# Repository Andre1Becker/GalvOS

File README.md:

# GalvOS

---

## What Is GalvOS?

GalvOS replaces the original control board of an RGB galvo laser projector (specifically the Mikoy 5W) with an ESP32-S3-based system. The result is a firmware platform that is more capable, fully open, and frankly more fun to work with than whatever the OEM shipped.

The origin story: the stock firmware couldn't dim the laser — it was full-brightness or nothing. What started as a quick bug investigation turned into a complete hardware and firmware replacement. Classic "Well, that escalated quickly..." moment.

**Key capabilities:**

- 16-bit galvo DAC (vs. OEM 12-bit) via SPI DAC8562
- Browser-based WebUI — no app install, works from any phone or desktop
- DMX-512, Art-Net, sACN/E1.31, and OSC input; Ether Dream and Helios (network) DAC protocols
- ILDA file playback from SD card
- Per-point laser modulation with full RGB PWM control
- BPM-synced show engine: global tempo clock (Tap/DMX/Manual), preset sequencer, and an 8-slot modulation matrix (LFO/Noise/Envelope/Step-Sequencer → any live pattern parameter)
- Watchdog, scan-command activity and E-stop interfaces — [safety qualification remains open](hardware/reviews/2026-09-14-shutdown-boundary.md)
- Point optimizer pipeline with adaptive density, S-curve blanking, and ringing compensation
- Camera-in-the-loop auto-tuning of optimizer parameters via a companion Python tool (see [Chapter 6](docs/06-camera-autotuning.md))
- Community Presets — browse, download, and activate GitHub-hosted preset bundles straight from the WebUI
- Temperature monitoring (up to 5× DS18B20 sensors)

---

## Full Feature List

Yes, all of this is real, and yes, it's all running on a 6 Freedom Money ($) microcontroller.
(That exclude all the other components you need - but hey, sounds much more impressive this way:-) )

### Output & Rendering

| Feature | What it does |
| --- | --- |
| 16-bit galvo DAC (DAC8562) | 4× the resolution of the OEM's 12-bit — lines that were jagged are now just... lines. |
| 9-stage point optimizer pipeline | Turns "draw a hexagon" into a stream the mirrors can physically survive — corner dwell, blanking, velocity/acceleration clamp, ZV ringing compensation. |
| 8 optimizer profiles (Vector, Smooth, Waves, Wireframe, MultiObject, Particles, Trails, Text) | One-size-fits-all optimizer settings don't exist, so pick per preset class instead. Auto-switches with the active preset. |
| Curvature-adaptive resampling | Spends points where the path actually bends and thins them out on straight runs, instead of pretending every millimetre is equally interesting. |
| Jump-order optimization (nearest-neighbour + 2-opt) | Reorders which segment gets drawn when, so the beam stops zigzagging across the canvas with the laser off. |
| Optimizer live telemetry | Lit/blank counts, truncated points, jump distance, which budget stage fired — tuning with numbers instead of vibes. |
| Smart Defaults button | Computes sane optimizer parameters from your kpps and frame budget. For when guessing sliders gets old. |
| Adjustable galvo sample rate (12–60 kpps) with Autotune | Binary-searches the highest rate your hardware handles before it starts buffering complaints. |
| CIE 1931 gamma correction | γ≈2.2 so "50% brightness" actually looks like 50% brightness to your eyeballs, not to a linear sensor. |
| Projection zone clipping | Draw a polygon, laser respects it. Points outside get blanked instead of redecorating your neighbor's wall. |
| Grid warp (keystone / surface correction) | Up to 5×5 control points to bend the image onto an off-axis or non-flat wall — corrects everything the projector draws, presets to ILDA files. |
| Brightness compensation grid | Same grid editor aimed at photons: evens out the exposure falloff you get from throw distance and angle. |
| Model-based inverse filter | Per-axis deconvolution of the galvo's measured resonance, applied to every point — the mirrors track the commanded path instead of ringing around it. |
| Output pre-scale | Shrinks the image proportionally so extreme corners stay in the galvo's linear range, instead of being flattened by the DAC clamp. |

### Patterns & Effects

| Feature | What it does |
| --- | --- |
| Built-in preset library (Geometry, Waves, 3D, Scenes, math curves) | A whole gallery of shapes so you don't have to parametrize a Lissajous curve at 2 AM. |
| Auto-rotation (independent X/Y/Z) + static rotation offset | Spin any pattern on any axis, at its own speed, because static geometry is for cowards. |
| 7 color animation modes (Gradient, Chase, Strobe, Pulse, Twinkle, Flip, Seg) | Layer a light show on top of any preset's own color without touching its code. |
| Points-Only Mode | Turns any pattern into a dot cloud with configurable fade-in/out and fade direction — instant particle show. |
| True Kaleidoscope (dihedral mirror-fold, 2/4/6-fold) + Radial Repeat mode & Mirror | Symmetric multiplication of whatever's on screen, because one hexagon is never enough. |
| Global BPM clock (Manual / Tap Tempo / DMX) | The whole show keeps a beat — priority DMX > Tap > Manual, with a big satisfying TAP button. |
| Preset Sequencer | A BPM-synced set list: walk presets step by step, beat-quantized, with optional blank transitions. Never auto-starts on boot — Class 4 lasers don't get autoplay. |
| Modulation engine (8 slots × 16 bindings) | LFOs, noise, multi-point envelopes, and step sequencers routed onto scale, rotation, hue, speed, density... Patterns that breathe on their own. |
| Modular modules: Camera, Duplicator, Spatial Noise, Dotter | Self-registering firmware modules that add 3D camera moves, frame cloning (grid/radial/spiral), organic wobble, and dot scatter — the UI discovers them automatically. |
| Freehand Paint tab | Draw with your finger or mouse, project it as vectors. Shape tools, mirror modes, undo/redo, and text insertion included for people who can't draw circles. |
| Laser Welding effect | A travelling torch head with a fading afterglow and ballistic sparks, rendered from the same Paint canvas. Pure theatre, and worth it. |
| SVG import | Load a vector drawing in the browser, simplify it to fit the point budget, and project it. Files can live on the SD card too. |
| Per-segment colors | Give a polygon or star a different color per edge, with an optional travelling animation. |
| Laser Text mode | 3 fonts, 10 animations (scroll, bounce, typewriter, Star Wars crawl,...), up to 127 characters. |
| Countdown timer with laser payoff | Set a timer, and when it hits zero: show text or fire off an ILDA file. Genuinely useful for events. |
| Community Presets (GitHub-hosted) | Browse a shared preset library straight from GitHub in the WebUI, download to the device, activate with one tap — each bundle carries a full optimizer tuning plus playback params. Now the internet can pick your colors too. |
| Community Preset Builder | Offline browser tool ([`community-presets/builder.html`](community-presets/builder.html)) for creating those bundles — for people who'd rather drag sliders than write C++. Advanced Mode even has a point/curve editor that exports C++ snippets for new built-in presets. |

### Control Inputs

| Feature | What it does |
| --- | --- |
| DMX-512 input (MAX485, 25 channels) | Talks to any real lighting desk like a grown-up fixture. |
| Art-Net input | DMX over Ethernet/Wi-Fi for the desk-less crowd. |
| sACN / E1.31 input | The standards-blessed way to do DMX over IP multicast. Same channel map, lowest priority of the three DMX-shaped sources. |
| OSC input | `/galvos/*` on UDP 9000 — preset, color, speed, brightness, and override from TouchOSC & friends. |
| Ether Dream protocol receiver | Laser software that speaks Ether Dream can stream point data straight to the projector. |
| Helios DAC network emulation | Helios point-stream framing over TCP 7768. The USB variant is not implemented (TinyUSB vendor class vs. the USB-CDC console). |
| Live software DMX console (WebUI) | 25 sliders, no physical desk required, with instant test patterns (red circle, rainbow). |
| WebUI override priority | WebUI wins over DMX on demand — for when you need to grab manual control mid-show. |
| Master dimmer (WebUI + DMX CH1 combined) | One dial to rule the overall brightness, regardless of source. |

### Storage & Playback

| Feature | What it does |
| --- | --- |
| ILDA file playback from SD card | Plays the industry-standard laser show format straight off a memory card — subfolders, live speed/size/color-override controls, browser upload included. |
| Playlist manager | Queue multiple ILDA files with per-entry loop count and pause duration. |
| PSRAM budget guard for ILDA files | Files too big to load safely are grayed out *before* you play them, instead of rebooting the controller mid-show. |
| SD auto-mount watcher | Insert a card whenever — it gets picked up within 5 seconds. Eject means eject, until you say otherwise. |
| SD file management from the browser | Download, rename, or delete `.ild` and `.svg` files on the card without pulling it out of the projector. |
| Independent SPI3 bus for SD | SD reads no longer corrupt the DAC output mid-frame — SD card lives on its own SPI3 bus (GPIO5/6/1/42), fully independent of the DAC's SPI2. |

### Calibration & Tuning

| Feature | What it does |
| --- | --- |
| Galvo geometry calibration | Offset, gain (linked X/Y), swap, invert — dial in a perfectly centered, correctly proportioned image. |
| Color/gamma calibration patterns | White fill, per-channel fill, three-circle white balance, crosshair, grid, DAC range box, official ILDA test pattern. |
| Visibility threshold calibration | Finds each laser diode's "dead zone" so 0–100% brightness maps to what's actually visible instead of a chunk of invisible PWM range. |
| Auto White Balance | Calculates per-channel gain from configured laser power so R/G/B actually look equally bright. |
| Camera-in-the-loop auto-tuning | A USB camera + Optuna search auto-tunes optimizer profiles against measured beam quality — no more "nudge a slider, squint at the wall" loop. See [Chapter 6](docs/06-camera-autotuning.md). |
| Resonance sweep | Drives one axis with a pure sine at a chosen frequency so you can actually measure the galvo's resonance instead of guessing at it. |

### Safety & Reliability

| Feature | What it does |
| --- | --- |
| Hardware E-Stop input | A physical kill switch the firmware cannot override. |
| NE555 scan-fail detection | If the galvo stops moving (or firmware hangs), the laser cuts — hardware-level, no software in the loop. |
| NE555 hardware watchdog | Independent of the ESP32's own watchdog; catches the case where the ESP32 itself locks up. |
| Fail-safe opto-isolated RGB TTL | 10kΩ pull-ups keep every laser channel OFF by default on boot, reset, panic, or brownout. |
| OTA update lockout while armed | Can't push new firmware to a live, armed laser. On purpose. |
| Browser OTA for firmware *and* WebUI | An `/update` page that flashes either partition, reports real error strings, and refuses to auto-reboot into a half-finished update. |
| Safety Assessment card | Live laser-class and audience-distance estimate from your configured power and beam angles. |
| Thermal protection | Up to 5× DS18B20 sensors with per-sensor names and calibration offsets, configurable warn/reduce/shutdown thresholds, auto or manual fan control, and a °C/°F/K display switch. |

### Connectivity & UI

| Feature | What it does |
| --- | --- |
| Browser-based WebUI, installable as a PWA | No app store, no native install — works full-screen from any phone, tablet, or desktop. |
| Three switchable themes | Cyberpunk/Glitch, Terminal CLI, Minimalist Dark — same controls, three personalities, zero flash-of-wrong-theme on reload. |
| Mobile-first safety controls | ARM/DISARM and Master Dimmer pinned in an always-visible top bar, 44 px touch targets — the kill switch never scrolls away. |
| Per-protocol debug logging | A "snitch switch" per network protocol (DMX, Art-Net, Ether Dream, Helios, OSC, sACN) — raw traffic straight into the Log tab. |
| Live Dashboard | Safety status, telemetry, CPU load, temperature history, DAC output rate, and frame composition — all scrolling in real time. |
| Live log console + memory viewer | Streamed over WebSocket, color-coded by severity, plus a heap/PSRAM breakdown by subsystem for hunting leaks. |
| Wi-Fi AP + STA mode, mDNS | Joins your network and answers at `galvOS.local`; falls back to its own WPA-protected access point when the network is unreachable, while still retrying in the background. |
| Static IP / DHCP configuration | For the tinfoil hatters who don't trust DHCP leases. |
| REST API with token auth | Full external control surface — see [API Reference](docs/08-api-reference.md). |
| Factory reset | Nukes all NVS config back to defaults when you've fat-fingered one setting too many. |

---

## Quick Start

Feeling yolo? Take this route then:

1. **Read the [Safety section](docs/01-introduction.md#safety--read-this-first)** — seriously.
2. **Check [Prerequisites](docs/02-prerequisites.md)** — tools and hardware needed.
3. **[Build & Flash](docs/03-build-and-config.md)** — PlatformIO build, firmware + WebUI upload.
4. **[Connect to WebUI](docs/04-ui-guide.md)** — Wi-Fi, browser, done.

No board on the bench yet? Try the WebUI first at **[www.galvos.de](https://www.galvos.de)** — see [Live Simulator](#live-simulator-no-hardware-required) below.

---

## Live Simulator (No Hardware Required)

**[www.galvos.de](https://www.galvos.de)** runs the exact WebUI as a self-contained browser simulation — a fake firmware backend behind the same frontend, no ESP32, no flashing, no install. Click around every tab, fire presets, tune the optimizer, and watch a simulated galvo trace respond, all before you own a single component. Handy for evaluating the UI, planning a build, or just seeing what the fuss is about.

It is **not** identical to a real device — no camera-in-the-loop tuning, no actual laser/galvo output, and it can lag a patch or two behind the firmware/UI shipped here (maintained by hand, see [Known Issues](docs/10-known-issues-and-todos.md#ui-issues)). For the real thing, [build one](docs/03-build-and-config.md).

---

## Documentation

Need a good sleep aid? This is the one for you here:

| Chapter | Description |
| --- | --- |
| [01 — Introduction](docs/01-introduction.md) | Project background, safety, disclaimer, hardware overview |
| [02 — Prerequisites](docs/02-prerequisites.md) | Tools, hardware, software, and skills needed |
| [03 — Build & Configuration](docs/03-build-and-config.md) | PlatformIO setup, all configurable parameters, flash instructions |
| [04 — UI Guide](docs/04-ui-guide.md) | Complete walkthrough of all WebUI tabs and controls |
| [05 — The Optimizer](docs/05-optimizer.md) | Deep-dive into the point optimizer pipeline |
| [06 — Auto-Tuning (CAM-based)](docs/06-camera-autotuning.md) | Automated optimizer tuning via `scripts/optimizeGalvo/optimizeGalvo.py` and a USB camera |
| [07 — Troubleshooting](docs/07-troubleshooting.md) | Common problems and how to solve them |
| [08 — API Reference](docs/08-api-reference.md) | REST API endpoints for integration and automation |
| [09 — Contributing](docs/09-contributing.md) | How to contribute, code style, patch workflow |
| [10 — Known Issues & To-dos](docs/10-known-issues-and-todos.md) | Open bugs, missing features, planned work |
| [11 — Glossary & Terminology](docs/11-glossary.md) | All (no but most) abbreviations and technical terms explained |

Release history: [CHANGELOG.md](CHANGELOG.md).

---

## Hardware at a Glance

Don't like one's and zero's that much? Well, this one is for you then:

| Component | Part |
| --- | --- |
| MCU | ESP32-S3-WROOM-1 N16R8 (16 MB Flash, 8 MB OPI PSRAM) |
| DAC | DAC8562 (16-bit, dual-channel, SPI) |
| Output Stage | OPA4134UA quad op-amp — differential ±5V galvo drive |
| Galvo Set | Jolooyo JY-15K-BL (15 kpps, ±20° optical) |
| Laser Driver | MN-1M5AT (3-channel constant-current buck, active-HIGH) |
| DMX | MAX485 module (receive-only, XLR) |
| Safety | NE555 scan-fail + NE555 hardware watchdog, 6N137 optocouplers |
| Temperature | DS18B20 × up to 5, 1-Wire bus |
| Power | HW-613 buck converter (+5V rail); external ±15V galvo PSU |
| Construction | Perfboard 15 × 9 cm; Gerber File for custom PCB is in progress |

Full netlist: [`hardware/`](hardware/)

---

## Repository Structure

```text
GalvOS/
├── src/                    # Firmware source (C++, Arduino/PlatformIO)
│   ├── control/            # DMX, Art-Net, safety control
│   ├── ilda/               # ILDA file parser
│   ├── net/                # WebUI server, REST API, Art-Net/sACN/OSC/Ether Dream/Helios receivers
│   ├── output/             # Galvo ISR, DAC output, RGB PWM
│   ├── patterns/           # Pattern engine, presets, optimizer
│   ├── safety/             # E-Stop, watchdog, scan-fail
│   ├── sensors/            # DS18B20, temperature monitoring
│   ├── storage/            # SD card, ILDA playlists, SVG storage
│   └── util/               # Shared utilities (log buffer, CPU/mem monitors, PSRAM scratch)
├── include/
│   ├── config.h            # Runtime config struct, optimizer defaults
│   └── pinmap.h            # All GPIO assignments
├── data/
│   └── index.html          # WebUI (single-file PWA, served via LittleFS)
├── community-presets/      # GitHub-hosted community preset library
│   ├── index.json          # Preset index fetched by the WebUI's GitHub Browser
│   ├── builder.html        # Community Preset Builder (offline browser tool, no backend)
│   └── *.json              # The preset bundles themselves
├── test/                   # Host-side (native) test suites
├── hardware/               # Netlist, schematics, wiring diagrams
├── scripts/
│   ├── upload_all.py       # PlatformIO target: flash firmware + LittleFS
│   ├── gzip_assets.py      # Pre-build hook: gzip data/ assets
│   ├── test_protocols.py   # Manual Ether Dream/Helios stream test client
│   └── optimizeGalvo/      # Camera-in-the-loop auto-tuning tool (see docs/06)
├── docs/                   # Full documentation (you are here)
│   ├── index.html          # Standalone WebUI simulator (served at galvos.de, no backend)
│   └── assets/             # Screenshots, diagrams, photos
├── platformio.ini          # Build configuration
└── partitions.csv          # Flash partition table
```

---

## ⚠️ SAFETY WARNING — READ BEFORE PROCEEDING

(I know - BORING! But hey - at least you read this far. So keep going!)

**This project involves CLASS IIIB or CLASS IV laser devices.**

Lasers at these power levels are capable of causing **immediate and permanent eye injury** and skin burns, and can ignite materials at close range.

- **Never** look into the beam or at specular (mirror-like) reflections.
- **Always** use appropriate laser safety eyewear — OD rating matched to your specific wavelengths and power level.
- **Never** operate the laser without proper enclosure or beam stops in place.
- By modifying this device, the original CE marking and safety certification are **void**.
- **You are solely responsible** for the safe operation of any device built using this project.
- Check your local laws — modifying laser equipment may require licensing in your jurisdiction.

> 🔴 **This project is intended for experienced makers and engineers who understand laser safety. Treat every beam as dangerous until proven otherwise.**

---

## License

- **Firmware & Software:** [GNU General Public License v3.0](LICENSE)
- **Hardware Designs:** [CERN Open Hardware License v2 — Strongly Reciprocal (CERN-OHL-S)](https://ohwr.org/cern_ohl_s_v2.txt)

Contributions welcome under the same license terms. See [Contributing](docs/09-contributing.md).

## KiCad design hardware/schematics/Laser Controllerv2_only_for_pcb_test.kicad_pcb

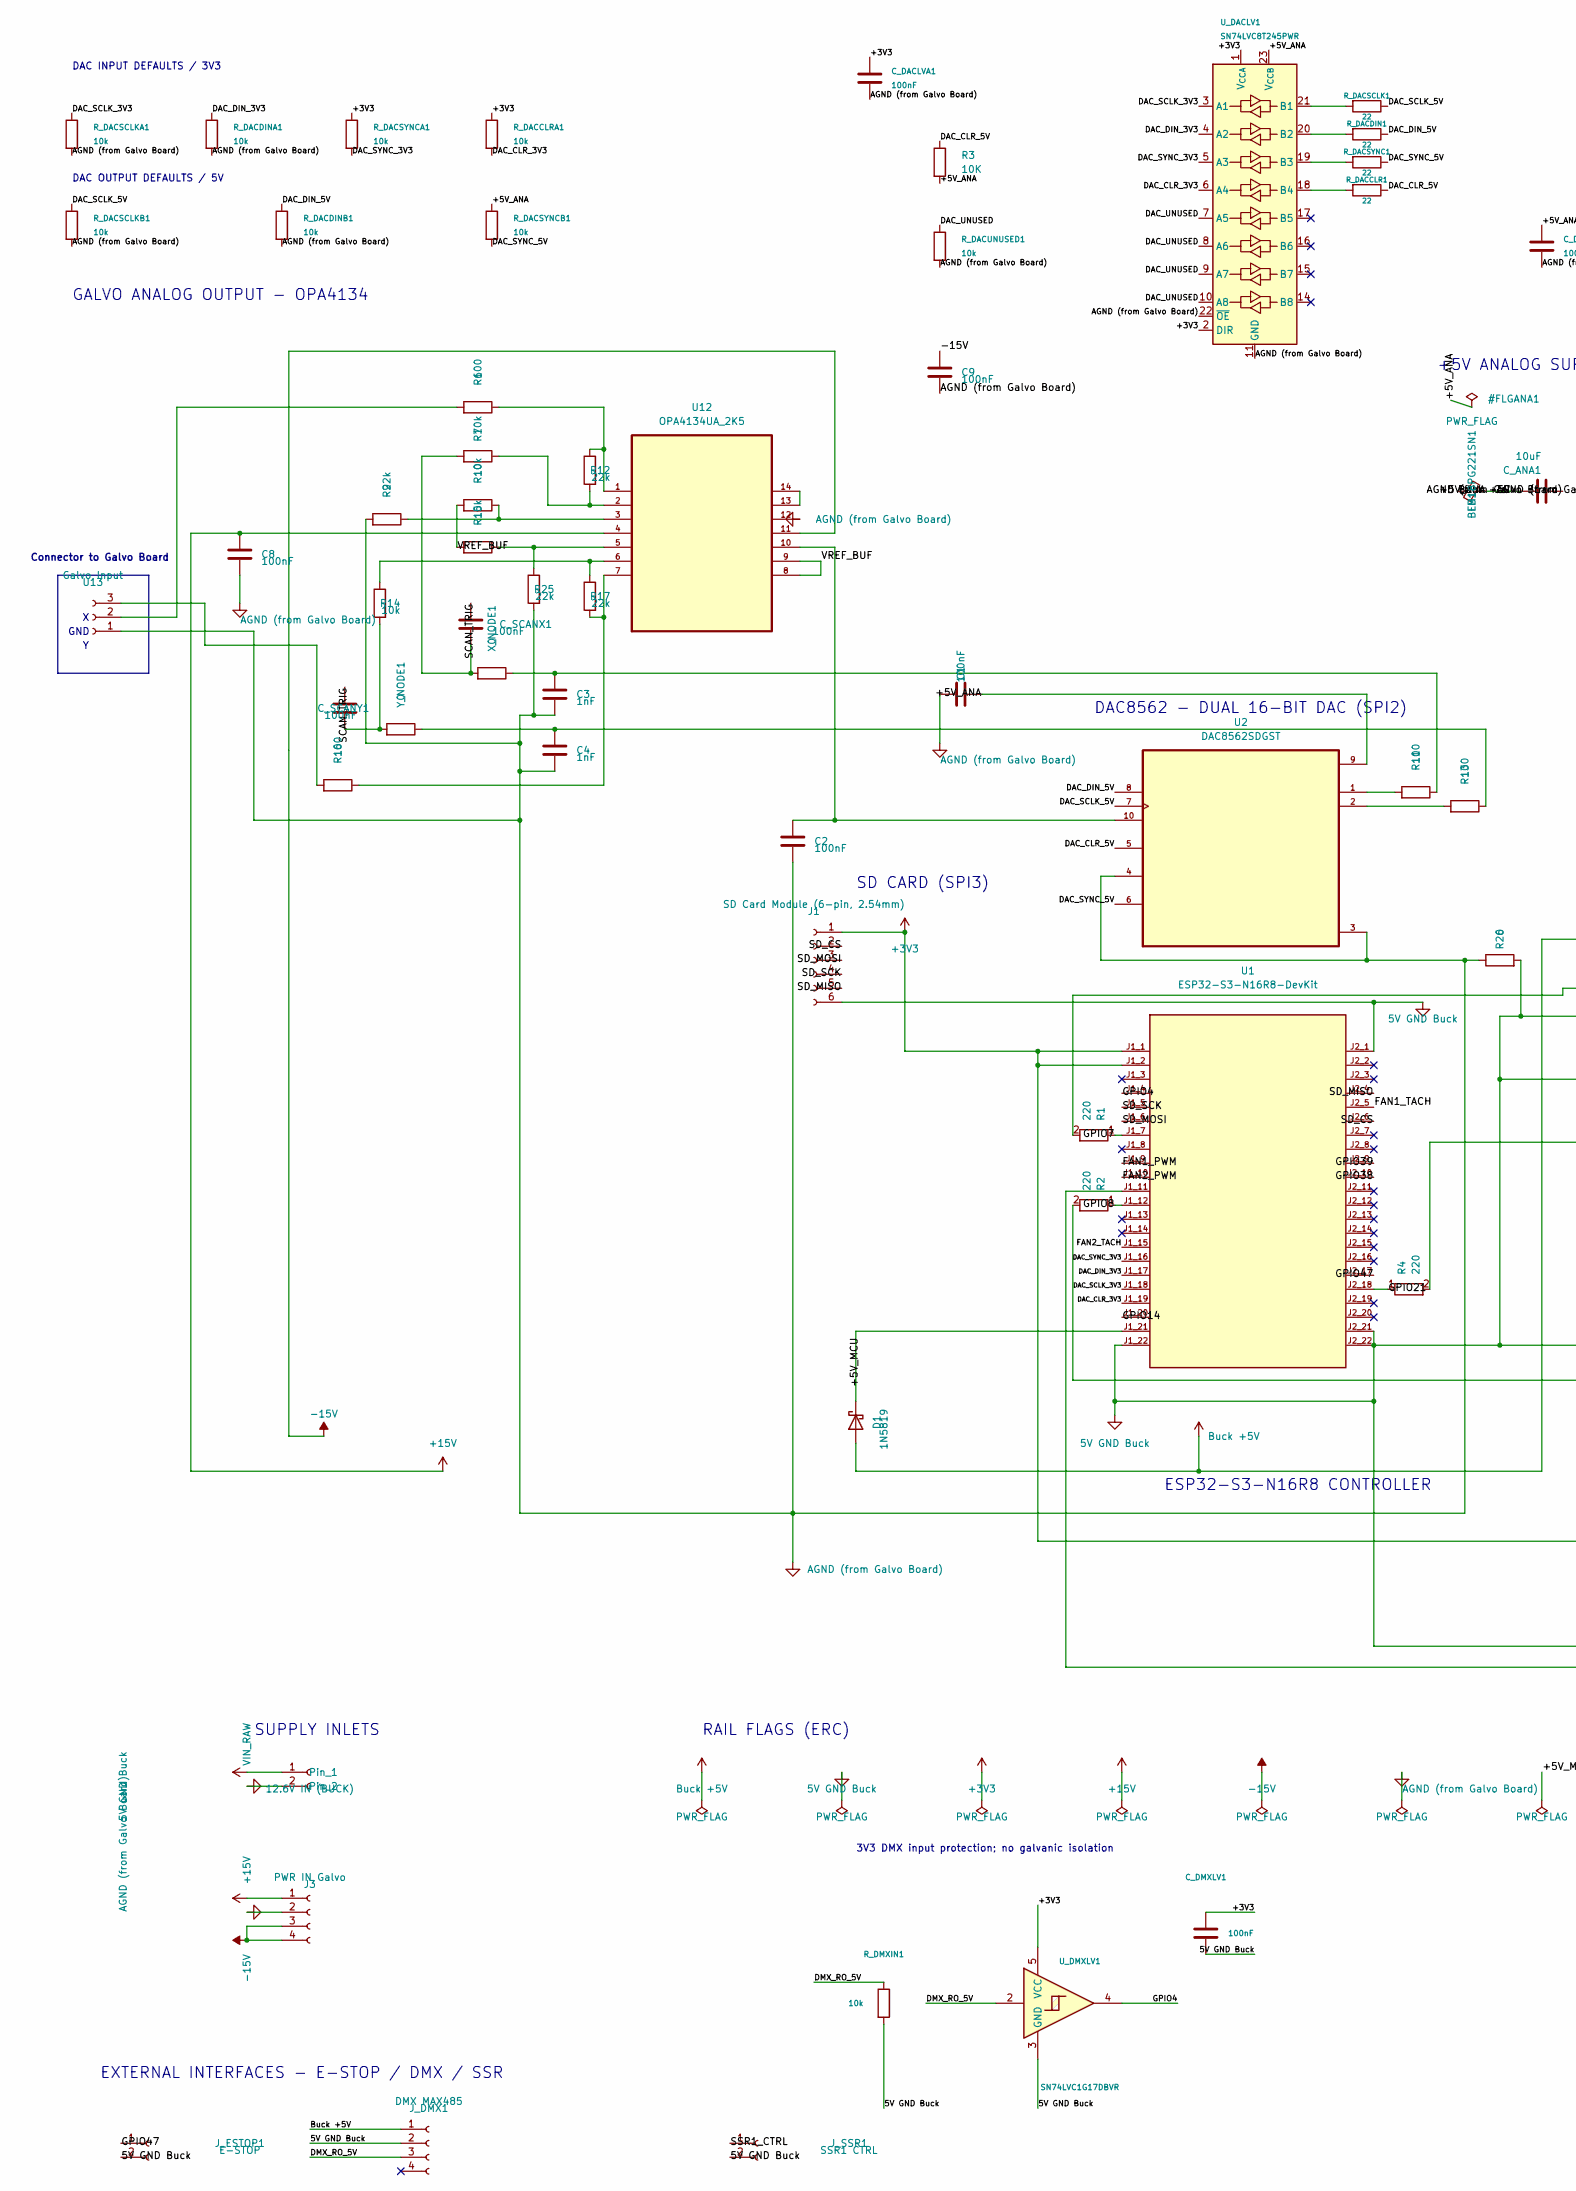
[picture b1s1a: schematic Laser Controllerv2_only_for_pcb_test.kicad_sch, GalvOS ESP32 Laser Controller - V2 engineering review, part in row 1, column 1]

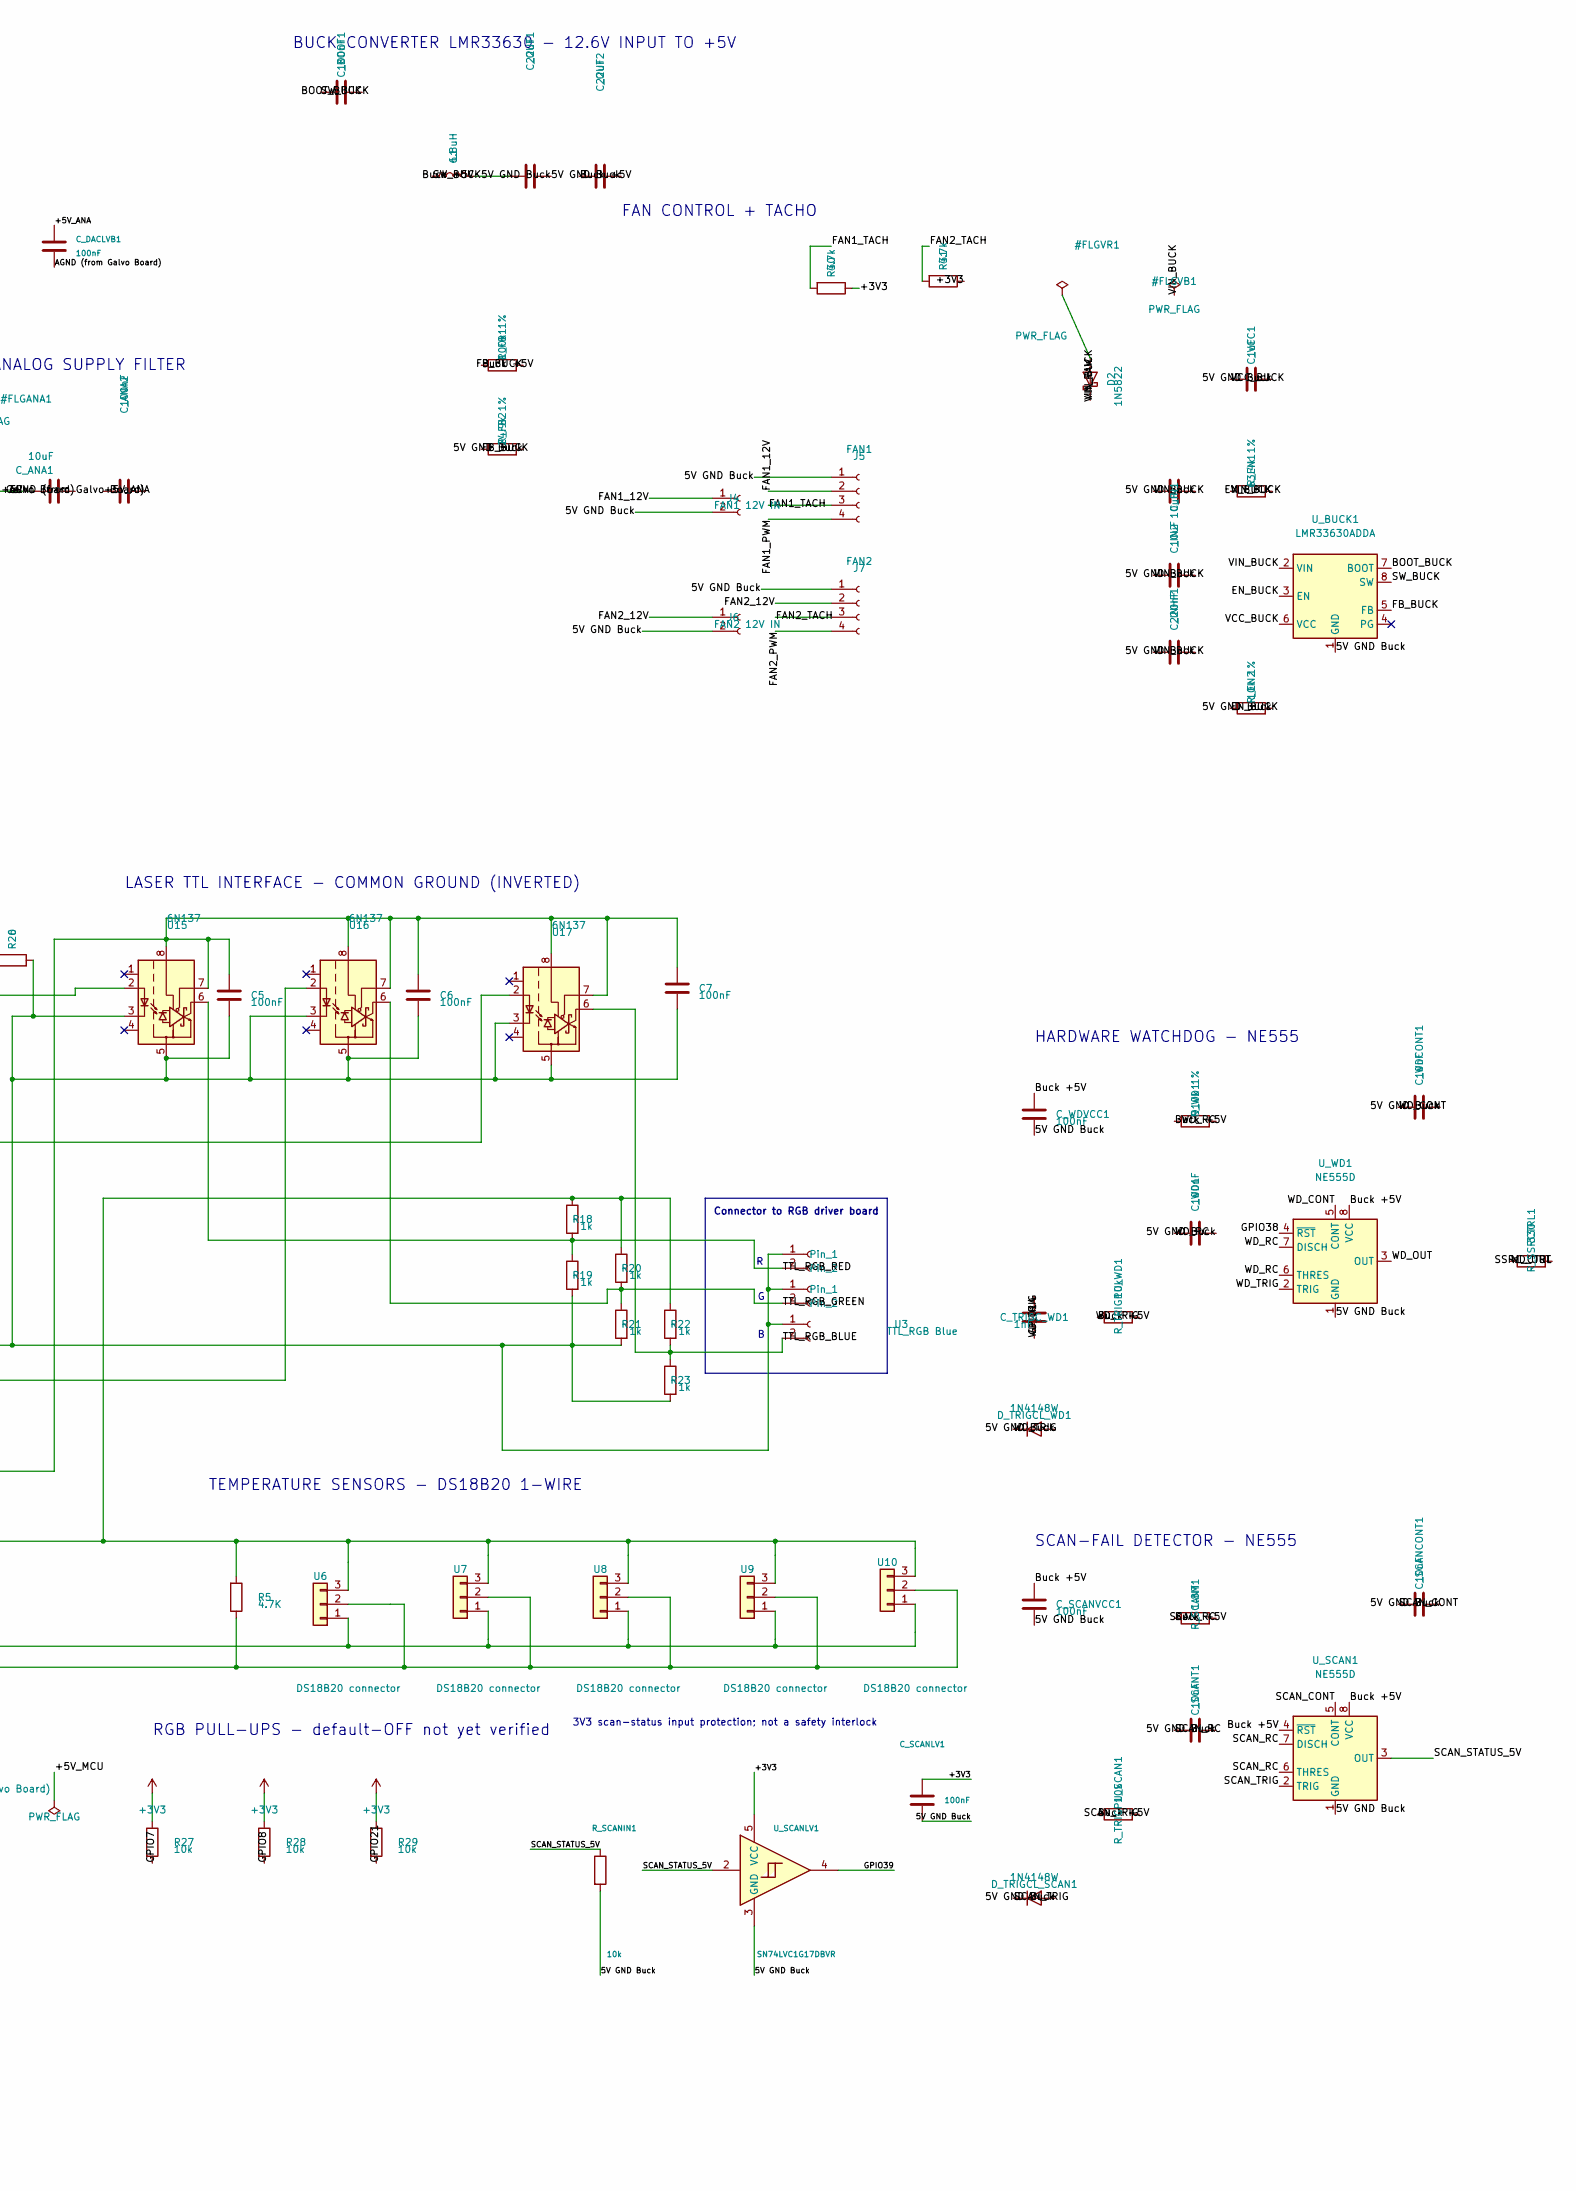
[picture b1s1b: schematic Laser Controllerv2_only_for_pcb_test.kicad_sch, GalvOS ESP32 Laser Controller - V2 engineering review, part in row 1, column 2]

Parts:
C1, C2, C5, C6, C7, C8: 100nF; C_1206_3216Metric
C3, C4: 1nF; C_1206_3216Metric
C9: 100nF; C_1206_3216Metric; Voltage 50V; Tolerance 10%
C_ANA1: 10uF; C_0805_2012Metric
C_ANA2: 100nF; C_1206_3216Metric
C_BOOT1: 100nF; C_1206_3216Metric; Voltage 16V; Tolerance 10%
C_DACLVA1: 100nF; C_1206_3216Metric; Voltage 50V; Tolerance 10%
C_DACLVB1: 100nF; C_1206_3216Metric; Voltage 50V; Tolerance 10%
C_DMXLV1: 100nF; C_1206_3216Metric; Voltage 50V; Tolerance 10%
C_IN1, C_IN2: 10uF; C_1210_3225Metric
C_INHF1: 220nF; C_1206_3216Metric; Voltage 50V; Tolerance 10%
C_OUT1, C_OUT2: 22uF; C_1206_3216Metric
C_SCANCONT1: 10nF; C_1206_3216Metric
C_SCANLV1: 100nF; C_1206_3216Metric; Voltage 50V; Tolerance 10%
C_SCANT1: 10nF; C_1206_3216Metric
C_SCANVCC1: 100nF; C_1206_3216Metric; Voltage 50V; Tolerance 10%
C_SCANX1: 100nF; C_1206_3216Metric
C_SCANY1: 100nF; C_1206_3216Metric
C_TRIGC_WD1: 1nF; C_1206_3216Metric
C_VCC1: 1uF; C_1206_3216Metric; Voltage 16V; Tolerance 10%
C_WD1: 100nF; C_1206_3216Metric
C_WDCONT1: 10nF; C_1206_3216Metric
C_WDVCC1: 100nF; C_1206_3216Metric; Voltage 50V; Tolerance 10%
D1: 1N5819; D_DO-41_SOD81_P10.16mm_Horizontal
D2: 1N5822; D_DO-201AD_P15.24mm_Horizontal
D_TRIGCL_SCAN1: 1N4148W; D_SOD-123; MPN 1N4148W-7-F
D_TRIGCL_WD1: 1N4148W; D_SOD-123; MPN 1N4148W-7-F
FB1: BLM18PG221SN1; L_0603_1608Metric
J1: SD Card Module (6-pin, 2.54mm); PinSocket_1x06_P2.54mm_Vertical
J2: 12.6V IN (BUCK); JST_XH_B2B-XH-A_1x02_P2.50mm_Vertical
J3: PWR IN Galvo; JST_XH_B4B-XH-A_1x04_P2.50mm_Vertical
J4: FAN1 12V IN; JST_XH_B2B-XH-A_1x02_P2.50mm_Vertical
J5: FAN1; Molex_KK-254_AE-6410-04A_1x04_P2.54mm_Vertical
J6: FAN2 12V IN; JST_XH_B2B-XH-A_1x02_P2.50mm_Vertical
J7: FAN2; Molex_KK-254_AE-6410-04A_1x04_P2.54mm_Vertical
J_DMX1: DMX MAX485; JST_XH_B4B-XH-A_1x04_P2.50mm_Vertical
J_ESTOP1: E-STOP; JST_XH_B2B-XH-A_1x02_P2.50mm_Vertical
J_SSR1: SSR1 CTRL; JST_XH_B2B-XH-A_1x02_P2.50mm_Vertical
L1: 6.8uH; L_Sunlord_MWSA1204S-6R8
R1, R2, R4: 220; R_1206_3216Metric
R3: 10K; R_1206_3216Metric
R5: 4.7K; R_1206_3216Metric
R6, R11, R13, R16: 100; R_1206_3216Metric
R7, R10, R14, R15, R27, R28, R29: 10k; R_1206_3216Metric
R9, R12, R17, R25: 22k; R_1206_3216Metric
R18, R19, R20, R21, R22, R23: 1k; R_1206_3216Metric
R26: 0; R_1206_3216Metric
R30, R31: 4.7k; R_1206_3216Metric
R_DACCLR1: 22; R_1206_3216Metric; Tolerance 1%
R_DACCLRA1: 10k; R_1206_3216Metric; Tolerance 1%
R_DACDIN1: 22; R_1206_3216Metric; Tolerance 1%
R_DACDINA1: 10k; R_1206_3216Metric; Tolerance 1%
R_DACDINB1: 10k; R_1206_3216Metric; Tolerance 1%
R_DACSCLK1: 22; R_1206_3216Metric; Tolerance 1%
R_DACSCLKA1: 10k; R_1206_3216Metric; Tolerance 1%
R_DACSCLKB1: 10k; R_1206_3216Metric; Tolerance 1%
R_DACSYNC1: 22; R_1206_3216Metric; Tolerance 1%
R_DACSYNCA1: 10k; R_1206_3216Metric; Tolerance 1%
R_DACSYNCB1: 10k; R_1206_3216Metric; Tolerance 1%
R_DACUNUSED1: 10k; R_1206_3216Metric; Tolerance 1%
R_DMXIN1: 10k; R_1206_3216Metric; Tolerance 1%
R_EN1: 63.4k 1%; R_1206_3216Metric
R_EN2: 10k 1%; R_1206_3216Metric
R_FB1: 100k 1%; R_1206_3216Metric; Tolerance 1%
R_FB2: 24.9k 1%; R_1206_3216Metric; Tolerance 1%
R_SCANIN1: 10k; R_1206_3216Metric; Tolerance 1%
R_SCANT1: 1.8M; R_1206_3216Metric
R_SSRCTRL1: 330; R_1206_3216Metric
R_TRIGPU_SCAN1: 10k; R_1206_3216Metric
R_TRIGPU_WD1: 10k; R_1206_3216Metric
R_WD1: 910k 1%; R_1206_3216Metric
U1: ESP32-S3-N16R8-DevKit; XCVR_ESP32-S3-N16R8-DevKit
U2: DAC8562SDGST; DGS10
U3: TTL_RGB Blue; JST_XH_B2B-XH-A_1x02_P2.50mm_Vertical
U4: TTL_RGB Red; JST_XH_B2B-XH-A_1x02_P2.50mm_Vertical
U5: TTL_RGB Green; JST_XH_B2B-XH-A_1x02_P2.50mm_Vertical
U6, U7, U8, U9, U10: DS18B20 connector; JST_XH_B3B-XH-A_1x03_P2.50mm_Vertical
U12: OPA4134UA_2K5; D14
U13: Galvo Input; JST_XH_B3B-XH-A_1x03_P2.50mm_Vertical
U15, U16, U17: 6N137; DIP-8_W7.62mm
U_BUCK1: LMR33630ADDA; Texas_HSOP-8-1EP_3.9x4.9mm_P1.27mm_ThermalVias
U_DACLV1: SN74LVC8T245PWR; TSSOP-24_4.4x7.8mm_P0.65mm; MPN SN74LVC8T245PWR
U_DMXLV1: SN74LVC1G17DBVR; SOT-23-5; MPN SN74LVC1G17DBVR
U_SCAN1: NE555D; SOIC-8_3.9x4.9mm_P1.27mm
U_SCANLV1: SN74LVC1G17DBVR; SOT-23-5; MPN SN74LVC1G17DBVR
U_WD1: NE555D; SOIC-8_3.9x4.9mm_P1.27mm
X_NODE1: 0; R_1206_3216Metric
Y_NODE1: 0; R_1206_3216Metric

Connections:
5V GND Buck: C5.2, C6.2, C7.2, C_DMXLV1.2, C_IN1.2, C_IN2.2, C_INHF1.2, C_OUT1.2, C_OUT2.2, C_SCANCONT1.2, C_SCANLV1.2, C_SCANT1.2, C_SCANVCC1.2, C_VCC1.2, C_WD1.2, C_WDCONT1.2, C_WDVCC1.2, D_TRIGCL_SCAN1.2 (A), D_TRIGCL_WD1.2 (A), J1.6, J2.2, J4.2, J5.1, J6.2, J7.1, J_DMX1.2, J_ESTOP1.2, J_SSR1.2, R19.2, R21.2, R23.2, R26.2, R_DMXIN1.2, R_EN2.2, R_FB2.2, R_SCANIN1.2, U1.J1_22 (GND), U1.J2_1 (GND), U1.J2_21 (GND), U1.J2_22 (GND), U3.1, U4.1, U5.1, U6.1, U7.1, U8.1, U9.1, U10.1, U15.3 (C), U15.5 (GND), U16.3 (C), U16.5 (GND), U17.3 (C), U17.5 (GND), U_BUCK1.1 (GND), U_BUCK1.9 (GND), U_DMXLV1.3 (GND), U_SCAN1.1 (GND), U_SCANLV1.3 (GND), U_WD1.1 (GND)
+3V3: C_DACLVA1.1, C_DMXLV1.1, C_SCANLV1.1, J1.1, R5.2, R18.1, R20.1, R22.1, R27.1, R28.1, R29.1, R30.1, R31.1, R_DACCLRA1.1, R_DACSYNCA1.1, U1.J1_1 (3V3), U1.J1_2 (3V3), U6.3, U7.3, U8.3, U9.3, U10.3, U_DACLV1.1 (V_{CCA}), U_DACLV1.2 (DIR), U_DMXLV1.5 (VCC), U_SCANLV1.5 (VCC)
+15V: C8.1, J3.1, U12.4 (V+)
-15V: C9.1, J3.3, J3.4, U12.11 (V-)
/+5V_ANA: C1.1, C_ANA1.1, C_ANA2.1, C_DACLVB1.1, FB1.2, R3.2, R_DACSYNCB1.1, U2.9 (AVDD), U_DACLV1.23 (V_{CCB}), U_DACLV1.24 (V_{CCB})
/+5V_MCU: D1.1 (K), U1.J1_21 (5V0)
/BOOT_BUCK: C_BOOT1.2, U_BUCK1.7 (BOOT)
/DAC_CLR_3V3: R_DACCLRA1.2, U1.J1_19 (GPIO13), U_DACLV1.6 (A4)
/DAC_CLR_5V: R3.1, R_DACCLR1.1, U2.5 (CLR)
/DAC_DIN_3V3: R_DACDINA1.1, U1.J1_17 (GPIO11), U_DACLV1.4 (A2)
/DAC_DIN_5V: R_DACDIN1.1, R_DACDINB1.1, U2.8 (DIN)
/DAC_SCLK_3V3: R_DACSCLKA1.1, U1.J1_18 (GPIO12), U_DACLV1.3 (A1)
/DAC_SCLK_5V: R_DACSCLK1.1, R_DACSCLKB1.1, U2.7 (SCLK)
/DAC_SYNC_3V3: R_DACSYNCA1.2, U1.J1_16 (GPIO10), U_DACLV1.5 (A3)
/DAC_SYNC_5V: R_DACSYNC1.1, R_DACSYNCB1.2, U2.6 (SYNC)
/DAC_UNUSED: R_DACUNUSED1.1, U_DACLV1.7 (A5), U_DACLV1.8 (A6), U_DACLV1.9 (A7), U_DACLV1.10 (A8)
/DMX_RO_5V: J_DMX1.3, R_DMXIN1.1, U_DMXLV1.2
/EN_BUCK: R_EN1.2, R_EN2.1, U_BUCK1.3 (EN)
/FAN1_12V: J4.1, J5.2
/FAN1_PWM: J5.4, U1.J1_9 (GPIO16)
/FAN1_TACH: J5.3, R30.2, U1.J2_5 (GPIO2)
/FAN2_12V: J6.1, J7.2
/FAN2_PWM: J7.4, U1.J1_10 (GPIO17)
/FAN2_TACH: J7.3, R31.2, U1.J1_15 (GPIO9)
/FB_BUCK: R_FB1.2, R_FB2.1, U_BUCK1.5 (FB)
/GPIO4: U1.J1_4 (GPIO4), U_DMXLV1.4
/GPIO7: R1.1, R27.2, U1.J1_7 (GPIO7)
/GPIO8: R2.1, R28.2, U1.J1_12 (GPIO8)
/GPIO14: C_TRIGC_WD1.1, U1.J1_20 (GPIO14)
/GPIO21: R4.1, R29.2, U1.J2_18 (GPIO21)
/GPIO38: U1.J2_10 (GPIO38), U_WD1.4 (~RST)
/GPIO39: U1.J2_9 (GPIO39), U_SCANLV1.4
/GPIO47: J_ESTOP1.1, U1.J2_17 (GPIO47)
/SCAN_CONT: C_SCANCONT1.1, U_SCAN1.5 (CONT)
/SCAN_RC: C_SCANT1.1, R_SCANT1.2, U_SCAN1.6 (THRES), U_SCAN1.7 (DISCH)
/SCAN_STATUS_5V: R_SCANIN1.1, U_SCAN1.3 (OUT), U_SCANLV1.2
/SCAN_TRIG: C_SCANX1.1, C_SCANY1.1, D_TRIGCL_SCAN1.1 (K), R_TRIGPU_SCAN1.2, U_SCAN1.2 (TRIG)
/SD_CS: J1.2, U1.J2_6 (GPIO42)
/SD_MISO: J1.5, U1.J2_4 (GPIO1)
/SD_MOSI: J1.3, U1.J1_6 (GPIO6)
/SD_SCK: J1.4, U1.J1_5 (GPIO5)
/SSR1_CTRL: J_SSR1.1, R_SSRCTRL1.2
/SW_BUCK: C_BOOT1.1, L1.1, U_BUCK1.8 (SW)
/TTL_RGB_BLUE: R22.2, R23.1, U3.2, U17.6 (VO)
/TTL_RGB_GREEN: R20.2, R21.1, U5.2, U16.6 (VO)
/TTL_RGB_RED: R18.2, R19.1, U4.2, U15.6 (VO)
/VCC_BUCK: C_VCC1.1, U_BUCK1.6 (VCC)
/VIN_BUCK: C_IN1.1, C_IN2.1, C_INHF1.1, D2.1 (K), R_EN1.1, U_BUCK1.2 (VIN)
/VREF_BUF: R10.2, R15.2, U12.8 (OUT_C), U12.9 (-IN_C)
/WD_CONT: C_WDCONT1.1, U_WD1.5 (CONT)
/WD_OUT: R_SSRCTRL1.1, U_WD1.3 (OUT)
/WD_RC: C_WD1.1, R_WD1.2, U_WD1.6 (THRES), U_WD1.7 (DISCH)
/WD_TRIG: C_TRIGC_WD1.2, D_TRIGCL_WD1.1 (K), R_TRIGPU_WD1.2, U_WD1.2 (TRIG)
AGND (from Galvo Board): C1.2, C2.2, C3.2, C4.2, C8.2, C9.2, C_ANA1.2, C_ANA2.2, C_DACLVA1.2, C_DACLVB1.2, J3.2, R9.2, R25.2, R26.1, R_DACDINA1.2, R_DACDINB1.2, R_DACSCLKA1.2, R_DACSCLKB1.2, R_DACUNUSED1.2, U2.3 (GND), U2.4 (LDAC), U12.12 (+IN_D), U13.1, U_DACLV1.11 (GND), U_DACLV1.12 (GND), U_DACLV1.13 (GND), U_DACLV1.22 (~OE)
Buck +5V: C5.1, C6.1, C7.1, C_OUT1.1, C_OUT2.1, C_SCANVCC1.1, C_WDVCC1.1, D1.2 (A), FB1.1, J_DMX1.1, L1.2, R_FB1.1, R_SCANT1.1, R_TRIGPU_SCAN1.1, R_TRIGPU_WD1.1, R_WD1.1, U15.7 (EN), U15.8 (VCC), U16.7 (EN), U16.8 (VCC), U17.7 (EN), U17.8 (VCC), U_SCAN1.4 (~RST), U_SCAN1.8 (VCC), U_WD1.8 (VCC)
unnamed: C3.1, R11.1, X_NODE1.1
unnamed: C4.1, R13.1, Y_NODE1.1
unnamed: C_SCANX1.2, R7.2, X_NODE1.2
unnamed: C_SCANY1.2, R14.2, Y_NODE1.2
unnamed: R5.1, U1.J1_11 (GPIO18), U6.2, U7.2, U8.2, U9.2, U10.2
unnamed: R11.2, U2.1 (VOUTA)
unnamed: R13.2, U2.2 (VOUTB)
unnamed: R9.1, R10.1, U12.3 (+IN_A)
unnamed: R15.1, R25.1, U12.5 (+IN_B)
unnamed: C2.1, U2.10 (VREFINNREFOUT), U12.10 (+IN_C)
unnamed: R7.1, R12.2, U12.2 (-IN_A)
unnamed: R14.1, R17.1, U12.6 (-IN_B)
unnamed: U12.13 (-IN_D), U12.14 (OUT_D)
unnamed: R6.1, R12.1, U12.1 (OUT_A)
unnamed: R16.1, R17.2, U12.7 (OUT_B)
unnamed: R6.2, U13.2
unnamed: R16.2, U13.3
unnamed: R1.2, U15.2 (A)
unnamed: R2.2, U16.2 (A)
unnamed: R4.2, U17.2 (A)
unnamed: R_DACSCLK1.2, U_DACLV1.21 (B1)
unnamed: R_DACDIN1.2, U_DACLV1.20 (B2)
unnamed: R_DACSYNC1.2, U_DACLV1.19 (B3)
unnamed: R_DACCLR1.2, U_DACLV1.18 (B4)
VIN_RAW: D2.2 (A), J2.1

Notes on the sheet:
Connector to RGB driver board
SUPPLY INLETS
Connector to Galvo Board
GND
RGB PULL-UPS - default-OFF not yet verified
RAIL FLAGS (ERC)
3V3 DMX input protection; no galvanic isolation
GALVO ANALOG OUTPUT - OPA4134
DAC8562 - DUAL 16-BIT DAC (SPI2)
+5V ANALOG SUPPLY FILTER
BUCK CONVERTER LMR33630 - 12.6V INPUT TO +5V
FAN CONTROL + TACHO
ESP32-S3-N16R8 CONTROLLER
SD CARD (SPI3)
LASER TTL INTERFACE - COMMON GROUND (INVERTED)
HARDWARE WATCHDOG - NE555
SCAN-FAIL DETECTOR - NE555
TEMPERATURE SENSORS - DS18B20 1-WIRE
EXTERNAL INTERFACES - E-STOP / DMX / SSR
3V3 scan-status input protection; not a safety interlock
DAC INPUT DEFAULTS / 3V3
DAC OUTPUT DEFAULTS / 5V

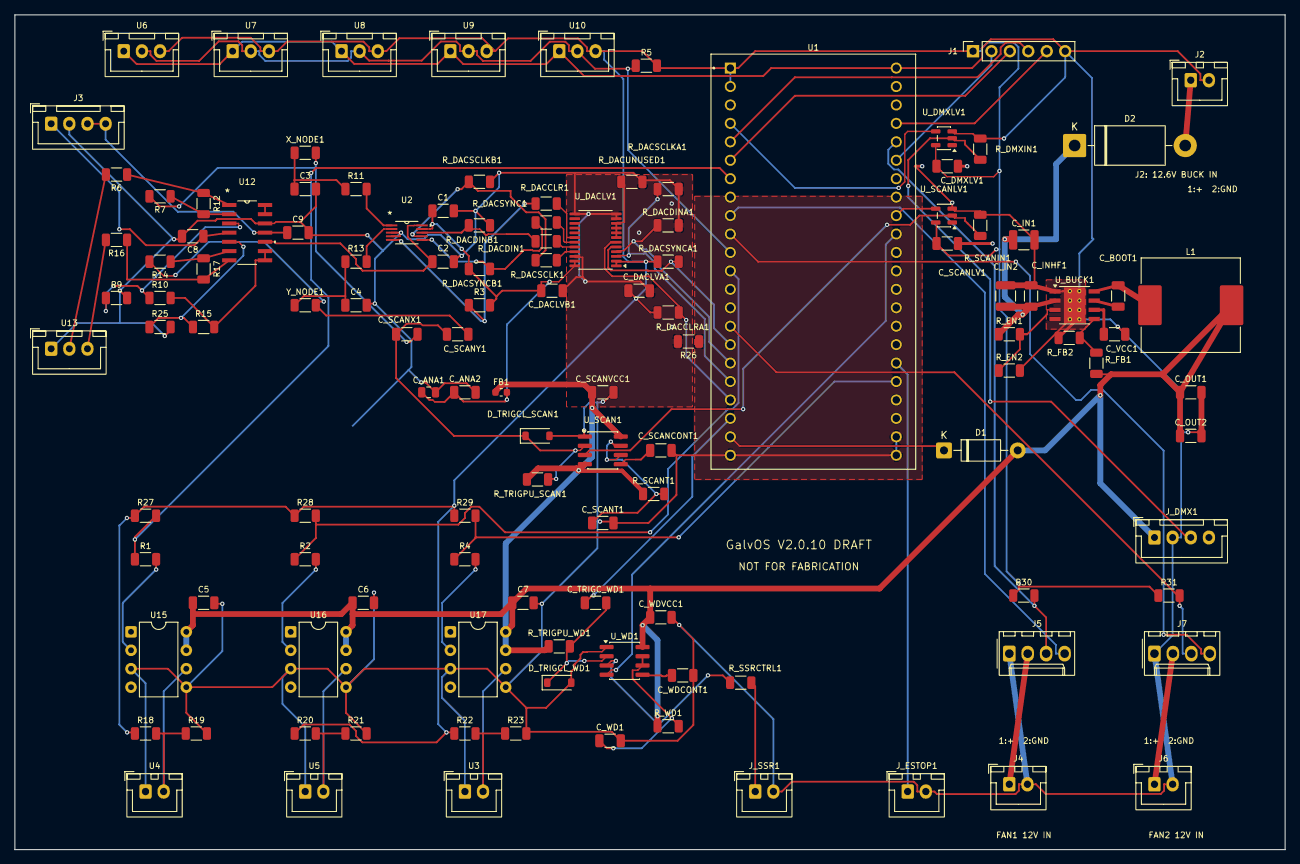
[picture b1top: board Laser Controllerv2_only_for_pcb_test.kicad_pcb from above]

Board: 2 copper layers, 175.0 x 115.0 mm, 122 parts (0 on the bottom side), 80 nets.

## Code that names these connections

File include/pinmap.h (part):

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 * ESP32-S3-DevKitC-1 J2 PINOUT (right side, 22 pins, verified from photo)
 * ───────────────────────────────────────────────────────────────────
 *  Pin  1: GND         Pin  2: GPIO43(TX)  Pin  3: GPIO44(RX)
 *  Pin  4: GPIO1(RTC)  Pin  5: GPIO2(RTC)
 *  Pin  6: GPIO42      Pin  7: GPIO41      Pin  8: GPIO40      Pin  9: GPIO39
 *  Pin 10: GPIO38      Pin 11: GPIO37      Pin 12: GPIO36      Pin 13: GPIO35
 *  Pin 14: GPIO0(BOOT) Pin 15: GPIO45      Pin 16: GPIO48      Pin 17: GPIO47
 *  Pin 18: GPIO21(RTC) Pin 19: GPIO20(USB_D+) Pin 20: GPIO19(USB_D-)
 *  Pin 21: GND         Pin 22: GND
 *  [NOTE: Pin1=GND, Pin19/20=USB reserved, Pin13=PSRAM internal]
 * ═══════════════════════════════════════════════════════════════════ */
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 * ESP32-S3-DevKitC-1 J1 PINOUT (left side, 22 pins, verified from photo)
 * ───────────────────────────────────────────────────────────────────
 *  Pin  1: 3V3        Pin  2: 3V3       Pin  3: RST
 *  Pin  4: GPIO4      Pin  5: GPIO5     Pin  6: GPIO6     Pin  7: GPIO7
 *  Pin  8: GPIO15     Pin  9: GPIO16    Pin 10: GPIO17    Pin 11: GPIO18
 *  Pin 12: GPIO8      Pin 13: GPIO3     Pin 14: GPIO46
 *  Pin 15: GPIO9      Pin 16: GPIO10    Pin 17: GPIO11    Pin 18: GPIO12
 *  Pin 19: GPIO13     Pin 20: GPIO14
 *  Pin 21: 5V0 (VIN)  Pin 22: GND
 * ═══════════════════════════════════════════════════════════════════ */

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
/* ============================================================
 * RGB TTL-Laser moduleation via LEDC-PWM
 * RGB: GPIO TTL via 6N137 optocouplers (GPIO7=R, GPIO8=G, GPIO21=B)
 * OPA4134 quad op-amp: galvo diff-amp X/Y + VREF unity buffer
 * PWM 100 kHz, 8-bit -> brightness via duty cycle (0=off, 255=full on)
 * 100Ω series resistor on each laser TTL input
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#define PIN_DMX_RX        4   /* MAX485 module RO → ESP32, UART1 RX */
// PIN_DMX_TX    removed — DMX receive only, no transmit
// PIN_DMX_DE_RE removed -- DE+RE of the module fixed to GND
// GPIO5, GPIO6 now free

/* ============================================================
 * Mode-Switch & Status
 * ============================================================ */
// PIN_MODE_SWITCH (GPIO1) removed -- physical ILDA interface/LF092 fallback droppedt (v3)
                              /* HIGH = ESP32 active, LOW = LF-092 active */
#define PIN_STATUS_LED   48   /* J2-Pin16 = GPIO48 */   /* Onboard-RGB-LED */

/* ============================================================
 * Safety Hardware
 * ============================================================ */
#define PIN_WATCHDOG_OUT 14   /* J1-Pin20 = GPIO14 */
#define PIN_ESTOP        47   /* J2-Pin17 = GPIO47 */   /* emergency stop status (active = not pressed) */
#define PIN_LASER_ENABLE 38   /* J2-Pin10 = GPIO38 */   /* central enable — HIGH only when all safety checks pass */
                              /* Goes to SSR/relay that releases the laser power rail */
#define PIN_SCAN_FAIL_IN 39   /* J2-Pin9  = GPIO39 */   /* NE555 Scan-Fail output (not yet populated) */

/* ============================================================
 * UI -- rotary encoder with button (no OLED display for now;
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 * J1-Header: PWM → Q1 (Fan 1), PWM → Q2 (Fan 2)
 * 25 kHz PWM, 8-bit. Minimum ~15% duty for reliable startup.
 * ============================================================ */
#define PIN_FAN1_PWM     16
#define PIN_FAN2_PWM     17

/* Fan tach (RPM) feedback -- 4-wire PC fan headers J5/J7 on the perfboard.
 * Open-drain output on the fan, 4.7kOhm pullup to +3V3 on-board (R30/R31).
 * Hardware-only for now: no ISR/pulse-counting firmware wired up yet. */
#define PIN_FAN1_TACH     2   /* J2-Pin5  = GPIO2  (was SD MISO, free) */
#define PIN_FAN2_TACH     9   /* J1-Pin15 = GPIO9  (was SD CS, free) */

/* ============================================================
 * Diagnostics / expansion
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/* ============================================================
 * SPI 3 (HSPI = independent GPSPI3 peripheral on ESP32-S3) -- SD card
 *
 * FIX vX.Y.Z: previously routed onto GPIO12/11/2/9 -- the same GPIOs
 * as the DAC8562's SPI2 bus. That was never a real "shared bus": on
 * ESP32-S3, Arduino's SPIClass(HSPI) is bound to the SPI3 hardware
 * peripheral (register base 0x60025000), NOT SPI2. Routing it onto
 * SPI2's pins just meant two *different* peripherals were both trying
 * to drive the same GPIOs via the GPIO matrix, which only lets ONE
 * peripheral signal own a given pin's output at a time -- whichever
 * side called SPIClass::begin() last silently stole GPIO12 (SCK) and
 * GPIO11 (MOSI) away from SPI2, disconnecting the DAC8562 from its own
 * clock/data lines. Whenever the SD card was actually transacting,
 * its real SPI3 traffic ended up on the DAC's SCK/MOSI pins instead --
 * root cause of "galvo goes erratic when a card is inserted".
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 * Fix: fully independent GPIOs, not just an independent peripheral.
 * No pin overlap with SPI2 at all -- zero interaction with the DAC.
 * ============================================================ */
#define PIN_SD_SCK         5   /* J1-Pin5  = GPIO5  */   /* SD card SCK  — dedicated SPI3 pin, no galvo overlap */
#define PIN_SD_MOSI        6   /* J1-Pin6  = GPIO6  */   /* SD card MOSI — dedicated SPI3 pin, no galvo overlap */
#define PIN_SD_MISO        1   /* J2-Pin4  = GPIO1  */   /* SD card MISO — dedicated SPI3 pin, no galvo overlap */
#define PIN_SD_CS         42   /* J2-Pin6  = GPIO42 */   /* SD card CS   — dedicated SPI3 pin, no galvo overlap */
// GPIO2 and GPIO9 (formerly SD MISO/CS) are now used for PIN_FAN1_TACH/PIN_FAN2_TACH above.

/* ILDA player config */
#define ILDA_MAX_FILES   40   /* Maximum count of .ild files on SD */
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
/* ── alias definitions for legacy code references ──────────────────── */
#define PIN_LASER_EN     PIN_LASER_ENABLE   /* emergencyStop alias */
// PIN_DAC_CLR_N (GPIO13, J1-Pin19): /CLR of DAC8562 (Pin5) — hardware pull-up 10kΩ
// In firmware GPIO13 is briefly pulsed LOW at init (CLR active) then HIGH (DAC active)
#define PIN_DAC_CLR_N    13   /* DAC8562 /CLR — J1-Pin19 = GPIO13 */

// Optional: hardware heartbeat for retriggerable blank failsafe
// #define PIN_HEARTBEAT  45  // uncomment if hardware is fitted
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

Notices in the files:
README.md:
License: GPL v3
Hardware License: CERN-OHL-S
